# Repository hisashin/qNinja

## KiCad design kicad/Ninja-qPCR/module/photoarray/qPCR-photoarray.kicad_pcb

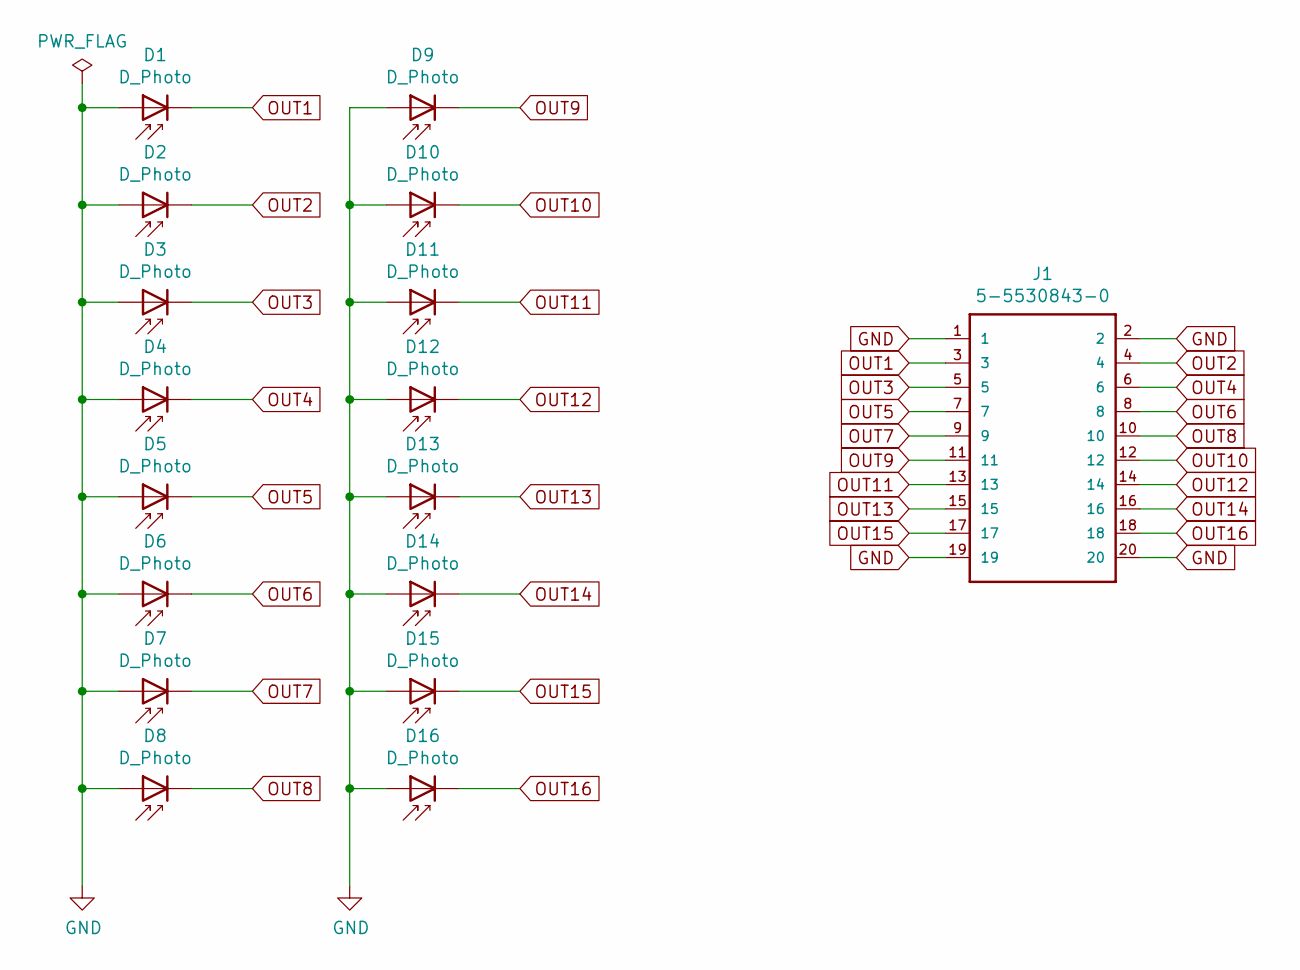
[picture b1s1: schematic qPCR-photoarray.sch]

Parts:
D1, D2, D3, D4, D5, D6, D7, D8, D9, D10, D11, D12, D13, D14, D15, D16: D_Photo; D_1206
J1: 5-5530843-0; TE_5-5530843-0-MALE

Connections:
GND: D1.2 (A), D2.2 (A), D3.2 (A), D4.2 (A), D5.2 (A), D6.2 (A), D7.2 (A), D8.2 (A), D9.2 (A), D10.2 (A), D11.2 (A), D12.2 (A), D13.2 (A), D14.2 (A), D15.2 (A), D16.2 (A); also elsewhere on the board
unnamed: J1.1, J1.2, J1.19, J1.20
OUT1: D1.1 (K), J1.3; also elsewhere on the board
OUT2: D2.1 (K), J1.4; also elsewhere on the board
OUT3: D3.1 (K), J1.5; also elsewhere on the board
OUT4: D4.1 (K), J1.6; also elsewhere on the board
OUT5: D5.1 (K), J1.7; also elsewhere on the board
OUT6: D6.1 (K), J1.8; also elsewhere on the board
OUT7: D7.1 (K), J1.9; also elsewhere on the board
OUT8: D8.1 (K), J1.10; also elsewhere on the board
OUT9: D9.1 (K), J1.11; also elsewhere on the board
OUT10: D10.1 (K), J1.12; also elsewhere on the board
OUT11: D11.1 (K), J1.13; also elsewhere on the board
OUT12: D12.1 (K), J1.14; also elsewhere on the board
OUT13: D13.1 (K), J1.15; also elsewhere on the board
OUT14: D14.1 (K), J1.16; also elsewhere on the board
OUT15: D15.1 (K), J1.17; also elsewhere on the board
OUT16: D16.1 (K), J1.18; also elsewhere on the board

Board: 2 copper layers, 17 parts (1 on the bottom side), 17 nets, no tracks yet.

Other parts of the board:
Je: 5-5530843-0; TE_5-5530843-0-MALE

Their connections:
GND: Je.1, Je.2, Je.19, Je.20; also elsewhere on the board
OUT1: Je.3; also elsewhere on the board
OUT2: Je.4; also elsewhere on the board
OUT3: Je.5; also elsewhere on the board
OUT4: Je.6; also elsewhere on the board
OUT5: Je.7; also elsewhere on the board
OUT6: Je.8; also elsewhere on the board
OUT7: Je.9; also elsewhere on the board
OUT8: Je.10; also elsewhere on the board
OUT9: Je.11; also elsewhere on the board
OUT10: Je.12; also elsewhere on the board
OUT11: Je.13; also elsewhere on the board
OUT12: Je.14; also elsewhere on the board
OUT13: Je.15; also elsewhere on the board
OUT14: Je.16; also elsewhere on the board
OUT15: Je.17; also elsewhere on the board
OUT16: Je.18; also elsewhere on the board

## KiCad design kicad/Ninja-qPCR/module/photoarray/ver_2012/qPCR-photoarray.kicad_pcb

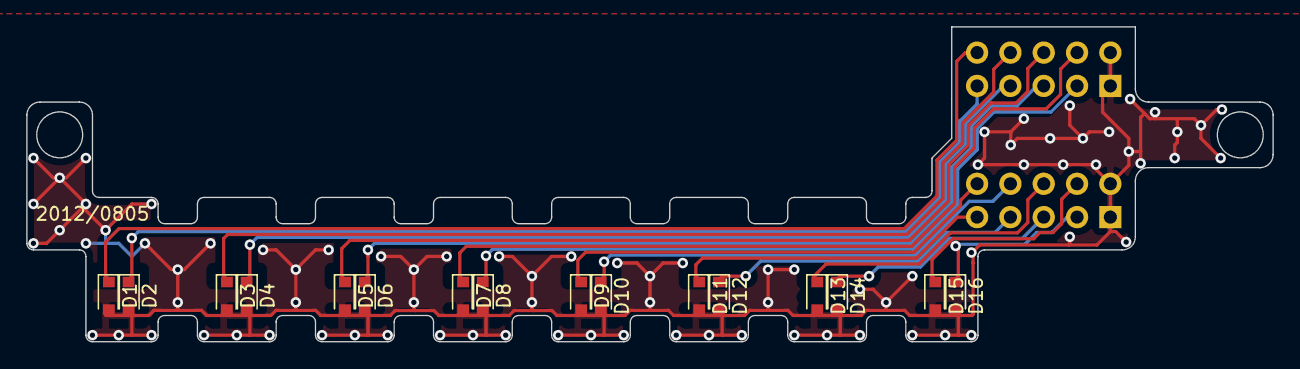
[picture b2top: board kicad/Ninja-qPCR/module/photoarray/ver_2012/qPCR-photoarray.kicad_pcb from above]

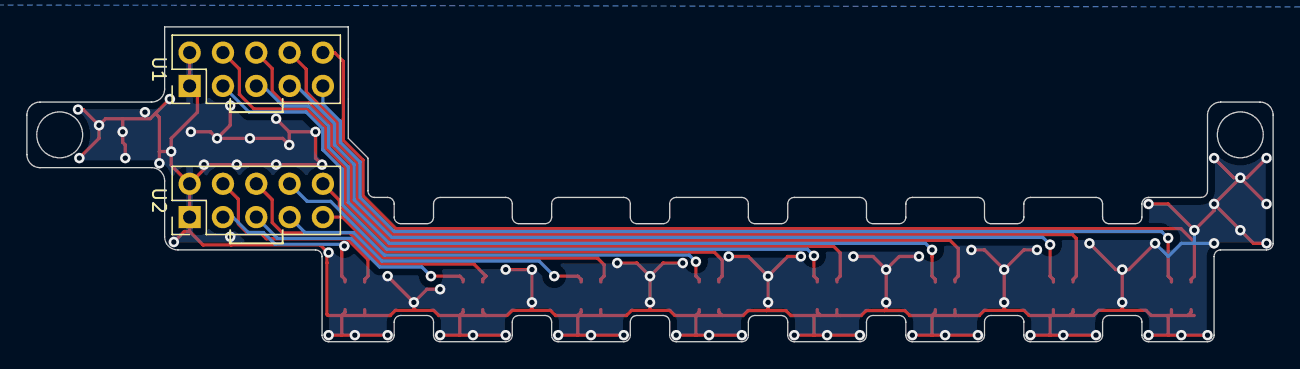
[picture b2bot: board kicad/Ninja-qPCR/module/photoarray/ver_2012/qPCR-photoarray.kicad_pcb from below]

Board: 2 copper layers, 95.0 x 24.0 mm, 18 parts (2 on the bottom side), 17 nets.

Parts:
D1, D2, D3, D4, D5, D6, D7, D8, D9, D10, D11, D12, D13, D14, D15, D16: D_Photo; D_0805
U1, U2: Conn_02x05; Pin_Header_Straight_2x05_Pitch2.54mm

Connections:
GND: D1.2, D2.2, D3.2, D4.2, D5.2, D6.2, D7.2, D8.2, D9.2, D10.2, D11.2, D12.2, D13.2, D14.2, D15.2, D16.2, U1.1, U1.2, U2.1, U2.2
OUT1: D1.1, U1.10
OUT2: D2.1, U1.9
OUT3: D3.1, U1.8
OUT4: D4.1, U1.7
OUT5: D5.1, U1.6
OUT6: D6.1, U1.5
OUT7: D7.1, U1.4
OUT8: D8.1, U1.3
OUT9: D9.1, U2.10
OUT10: D10.1, U2.8
OUT11: D11.1, U2.9
OUT12: D12.1, U2.7
OUT13: D13.1, U2.6
OUT14: D14.1, U2.5
OUT15: D15.1, U2.4
OUT16: D16.1, U2.3

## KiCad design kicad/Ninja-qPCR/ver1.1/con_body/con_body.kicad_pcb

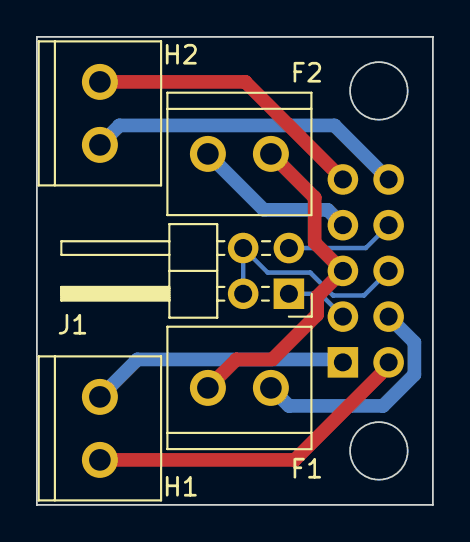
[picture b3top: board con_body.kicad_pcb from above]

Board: 2 copper layers, 22.0 x 26.0 mm, 6 parts (1 on the bottom side), 10 nets.

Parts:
F1, F2: Screw_Terminal_01x02; TB_SeeedOPL_320110028
H1, H2: Screw_Terminal_01x02; TB_SeeedOPL_320110028
J1: Conn_01x04_Male; Pin_Header_Angled_2x02_Pitch2.54mm
U1: Conn_02x05; Pin_Header_Straight_2x05_Pitch2.54mm

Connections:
FAN1: F1.2, U1.4
FAN2: F2.2, U1.7
FAN_VCC: F1.1, F2.1, U1.5
HEATER1A: H1.1, U1.1
HEATER1B: H1.2, U1.2
HEATER2A: H2.1, U1.9
HEATER2B: H2.2, U1.10
THERM1: J1.1, U1.3
THERM2: J1.3, U1.8
THERM_GND: J1.2, J1.4, U1.6

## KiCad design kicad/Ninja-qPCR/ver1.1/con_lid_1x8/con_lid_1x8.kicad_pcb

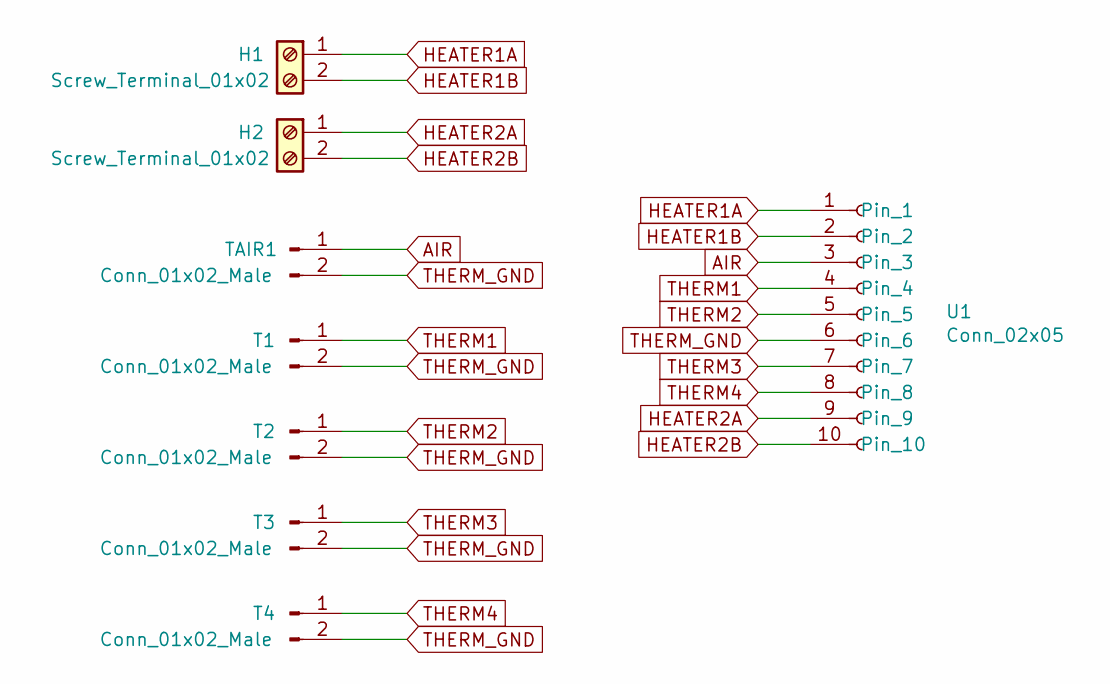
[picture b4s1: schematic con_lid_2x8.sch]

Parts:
H1, H2: Screw_Terminal_01x02; TB_SeeedOPL_320110028
T1, T2, T3, T4: Conn_01x02_Male; Pin_Header_Angled_1x02_Pitch2.54mm
TAIR1: Conn_01x02_Male; Pin_Header_Angled_1x02_Pitch2.54mm
U1: Conn_02x05; Pin_Header_Straight_2x05_Pitch2.54mm

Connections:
AIR: TAIR1.1, U1.3
HEATER1A: H1.1, U1.1
HEATER1B: H1.2, U1.2
HEATER2A: H2.1, U1.9
HEATER2B: H2.2, U1.10
THERM1: T1.1, U1.4
THERM2: T2.1, U1.5
THERM3: T3.1, U1.7
THERM4: T4.1, U1.8
THERM_GND: T1.2, T2.2, T3.2, T4.2, TAIR1.2, U1.6

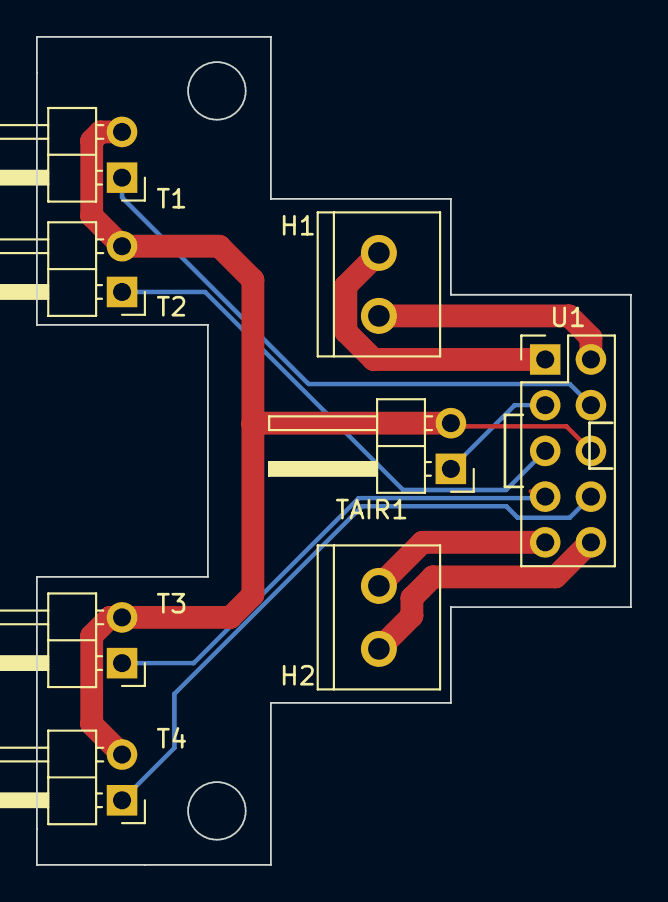
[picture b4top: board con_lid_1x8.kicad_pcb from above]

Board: 2 copper layers, 33.0 x 46.0 mm, 8 parts (0 on the bottom side), 10 nets.
